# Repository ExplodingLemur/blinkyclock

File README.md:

This was supposed to be a simple red/green clock to indicate when our office security system swapped from unlocked to badge-required.

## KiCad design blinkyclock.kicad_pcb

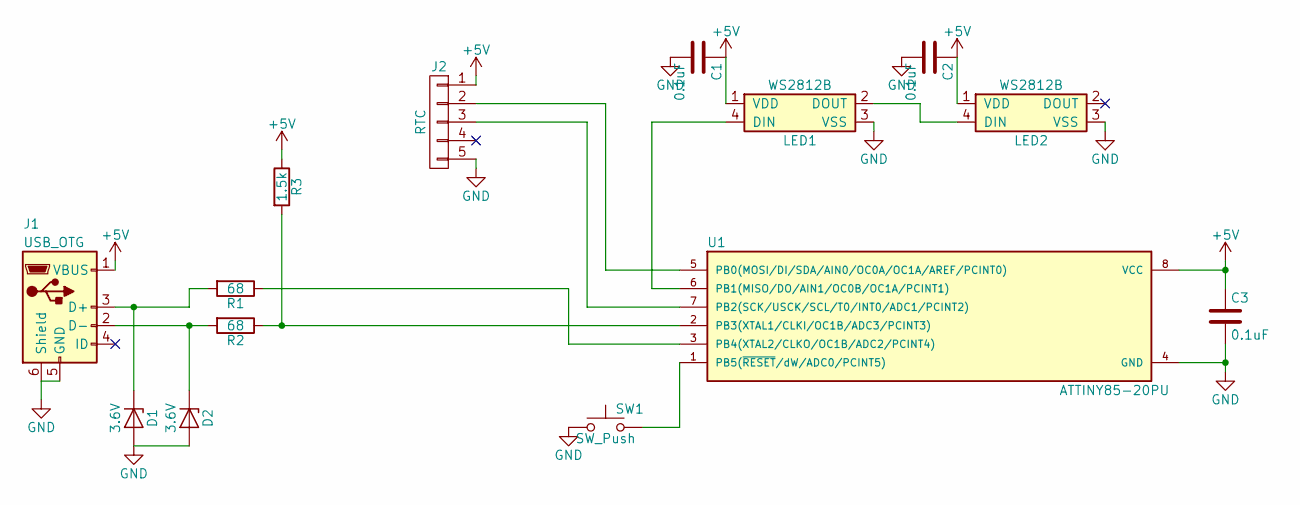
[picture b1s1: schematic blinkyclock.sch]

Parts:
C1, C2, C3: 0.1uF; C_0805_HandSoldering
D1, D2: 3.6V; D_0805
J1: USB_OTG; USB_Mini-B
J2: RTC; Pin_Header_Straight_1x05_Pitch2.54mm
LED1, LED2: WS2812B; LED_WS2812B-PLCC4
R1, R2: 68; R_0805_HandSoldering
R3: 1.5k; R_0805_HandSoldering
SW1: SW_Push; SW_SPST_EVPBF
U1: ATTINY85-20PU; SOIC-8_3.9x4.9mm_Pitch1.27mm

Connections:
+5V: C1.1, C2.1, C3.1, J1.1 (VBUS), J2.1, LED1.1 (VDD), LED2.1 (VDD), R3.1, U1.8 (VCC)
GND: C1.2, C2.2, C3.2, D1.2 (A), D2.2 (A), J1.5 (GND), J1.6 (Shield), J2.5, LED1.3 (VSS), LED2.3 (VSS), SW1.1, U1.4 (GND)
unnamed: D1.1 (K), J1.3 (D+), R1.2
unnamed: D2.1 (K), J1.2 (D-), R2.2
unnamed: J2.2, U1.5 (PB0(MOSI/DI/SDA/AIN0/OC0A/OC1A/AREF/PCI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)
unnamed: J2.3, U1.7 (PB2(SCK/USCK/SCL/T0/INT0/ADC1/PCINT2))
unnamed: LED1.2 (DOUT), LED2.4 (DIN)
unnamed: LED1.4 (DIN), U1.6 (PB1(MISO/DO/AIN1/OC0B/OC1A/PCINT1))
unnamed: R1.1, U1.3 (PB4(XTAL2/CLKO/OC1B/ADC2/PCINT4))
unnamed: R2.1, R3.2, U1.2 (PB3(XTAL1/CLKI/OC1B/ADC3/PCINT3))
unnamed: SW1.2, U1.1 (PB5(~RESET~/dW/ADC0/PCINT5))

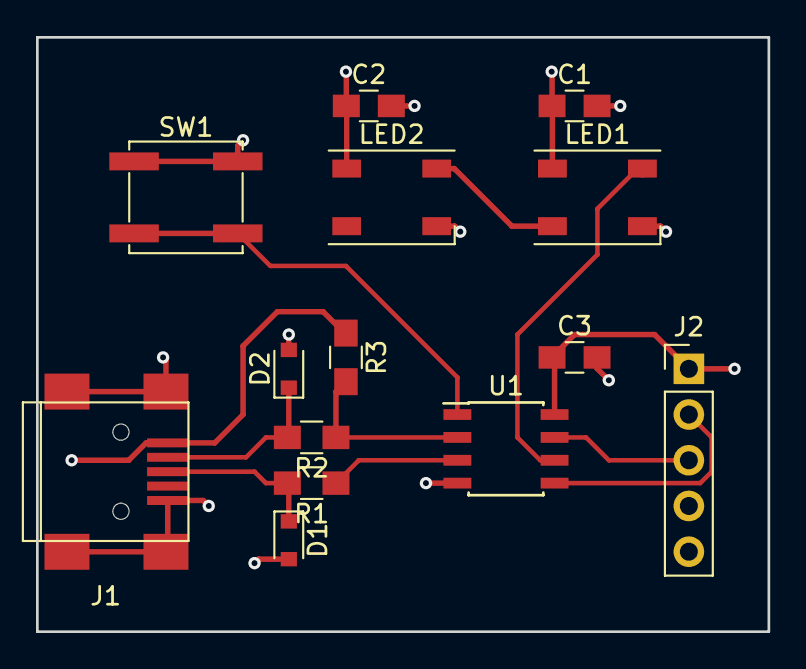
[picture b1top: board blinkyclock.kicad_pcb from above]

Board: 2 copper layers, 40.6 x 33.0 mm, 14 parts (0 on the bottom side), 11 nets.

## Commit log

2017-05-13 first rev in progress
2017-05-13 finished layout
